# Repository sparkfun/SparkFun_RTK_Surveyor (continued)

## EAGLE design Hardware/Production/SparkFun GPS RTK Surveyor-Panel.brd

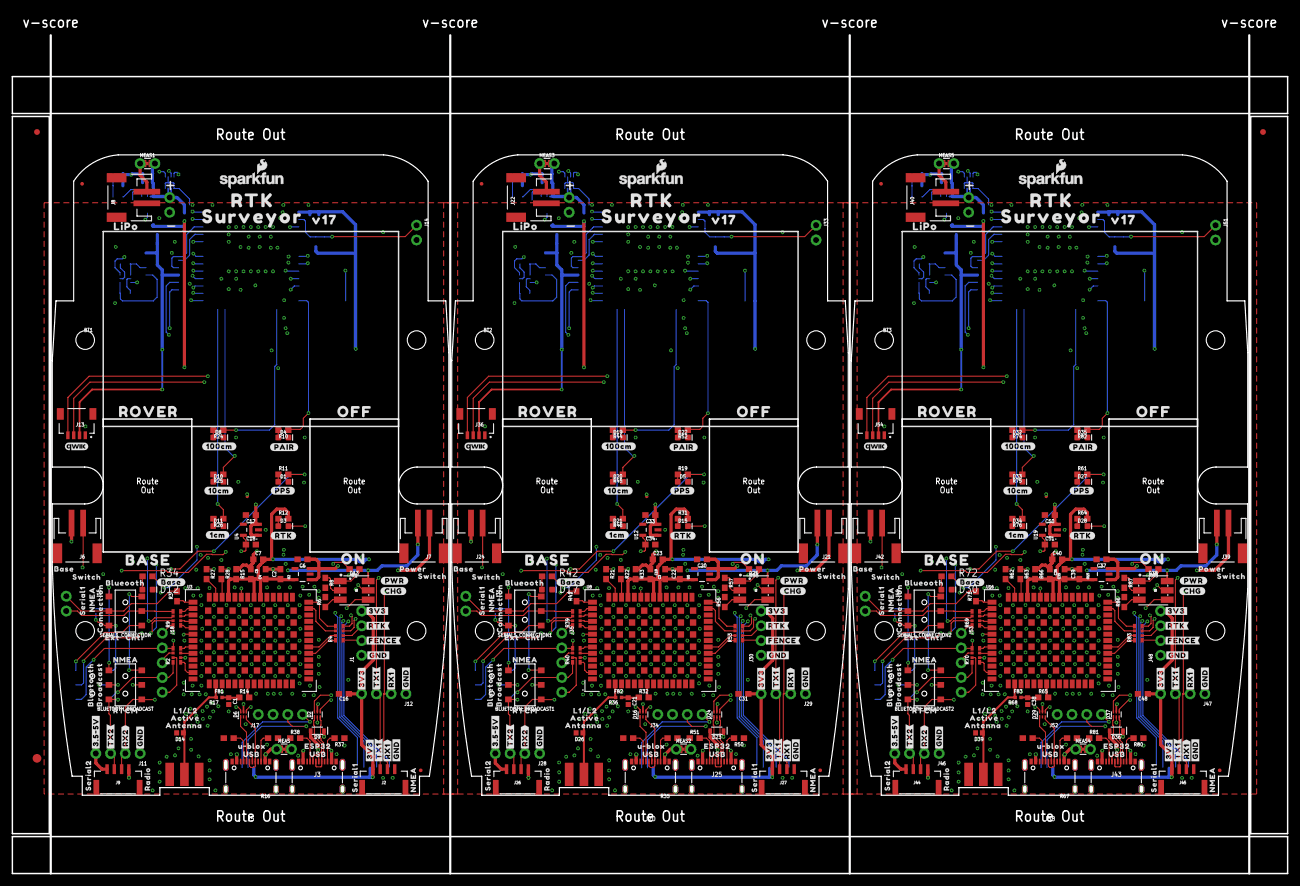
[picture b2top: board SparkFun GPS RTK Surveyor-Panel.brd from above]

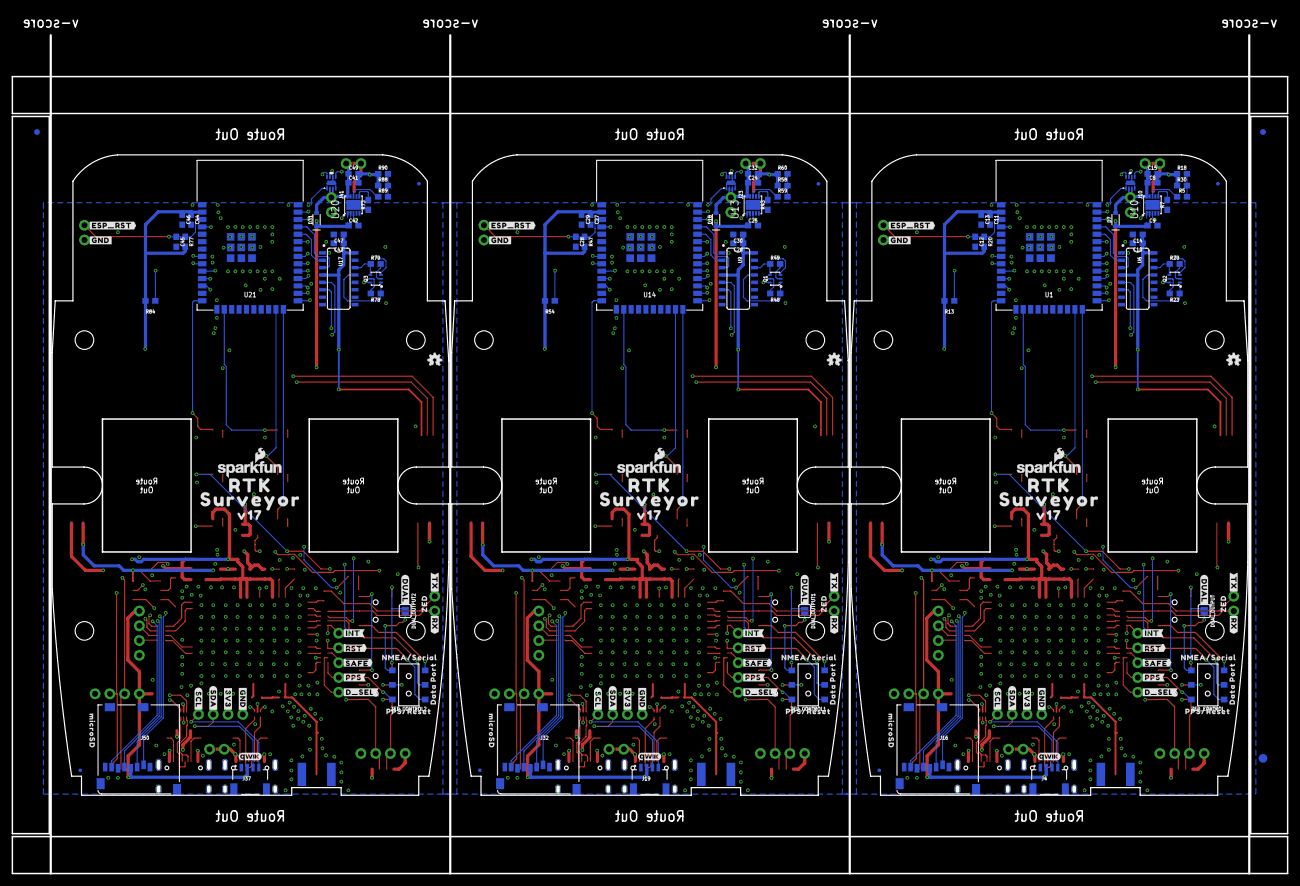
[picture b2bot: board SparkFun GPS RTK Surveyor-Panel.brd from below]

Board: 4 copper layers, 219.3 x 144.2 mm, 594 parts (168 on the bottom side), 285 nets.

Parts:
BLUETOOTH_BROADCAST, BLUETOOTH_BROADCAST1, BLUETOOTH_BROADCAST2: SWITCH_DPDT_SMD_AYZ0202
BT1, BT2, BT3: LIPO-OUTLINE1000; LIPO-1000
C1, C21, C38: 47pF; 0402
C2, C3, C4, C6, C17, C18, C20, C22, C33, C34, C35, C37, C39, C50, C51: 1.0uF; 0603
C5, C7, C11, C12, C13, C15, C16, C19, C23, C27, C28, C29, C31, C32, C36, C40, C44, C45, C46, C48, C49: 0.1uF; 0603
C8, C9, C24, C25, C41, C42: 4.7uF; 0603
C10, C14, C26, C30, C43, C47: 10uF; 0603
D1, D5, D27: Yellow; LED-0603
D2, D6, D16, D24, D29, D37: PRTR5V0U2F; SOT886
D3, D15, D28: WHITE; LED-0603
D4, D22, D35: BLUE; LED-0603
D7, D9, D18, D23, D31, D36: 3A/10V/280mV; SOD-323
D8, D10, D11, D19, D20, D21, D32, D33, D34: GREEN; LED-0603
D12, D17, D30: RED; LED-0603
D13, D25, D38: LED-TRICOLOR-5050
D14, D26, D39: PESD0402; 0402
DUAL_OUTPUT, DUAL_OUTPUT1, DUAL_OUTPUT2: SMT-JUMPER_2_NO_SILK
E1, E2, E3: SMA; SMA-EDGE
E$1, E$2, E$3, E$4: FIDUCIAL-1X2
E$5, E$6: FIDUCIAL-1.5X3
FB1, FB2, FB3: 2.66Ω; 0402-TIGHT
J1, J11, J12, J28, J29, J30, J46, J47, J48: 1X04_NO_SILK
J2, J9, J26, J27, J44, J45: JST-4-SMD-1.25MM-LOCKING
J3, J5, J20, J25, J38, J43: USB Female Type C Connector; USB-C-16P_4LAYER-PADS
J4, J19, J37: External; JST04_1MM_RA
J6, J24, J42: Start Base; JST-2-SMD
J7, J21, J39: Power Switch; JST-2-SMD
J8, J22, J40: JST-2-SMD
J10, J14, J15, J23, J31, J33, J41, J49, J51: 1X02_NO_SILK
J13, J36, J54: Internal; JST04_1MM_RA
J16, J32, J50: microSD; MICRO-SD-SOCKET
J17, J34, J52: Qwiic Right Angle; 1X04_NO_SILK
J18, J35, J53: 1X05_NO_SILK
JP1, JP2, JP3, JP4, JP5, JP6, JP7, JP8, JP21, JP61, JP71, JP81: FIDUCIALUFIDUCIAL; FIDUCIAL-MICRO
LOGO1, LOGO4, LOGO7: OSHW-LOGOMINI; OSHW-LOGO-MINI
LOGO2, LOGO3, LOGO5, LOGO6, LOGO8, LOGO9: SFE_LOGO_NAME_FLAME.1_INCH; SFE_LOGO_NAME_FLAME_.1
MEAS, MEAS1, MEAS2, MEAS3, MEAS4, MEAS5: COMBO-JUMPER_2_NC_TRACE
Q1, Q2, Q3: MBT3904DW1T1; SC70-6
R1, R55, R85: 4.7k; 0603
R2, R4, R9, R39, R40, R53, R69, R70, R83: 33; 1206_RA
R3, R41, R71: 33; 0603
R5, R59, R89: 0; 0603
R6, R7, R8, R43, R56, R57, R73, R86, R87: 1k; 0603
R10, R12, R31, R34, R42, R52, R64, R72, R82: 330; 0603
R11, R19, R24, R25, R26, R44, R45, R46, R61, R74, R75, R76: 20; 0603
R13, R15, R33, R54, R66, R84: 100k; 0603
R14, R32, R65: 10; 0603
R16, R17, R35, R36, R37, R38, R50, R51, R67, R68, R80, R81: 5.1k; 0603
R18, R20, R23, R29, R47, R48, R49, R60, R77, R78, R79, R90: 10k; 0603
R21, R22, R27, R28, R62, R63: 27; 0603
R30, R58, R88: 150k; 0603
SERIAL1_CONNECTION, SERIAL1_CONNECTION1, SERIAL1_CONNECTION2: SWITCH_DPDT_SMD_AYZ0202
U1, U14, U21: ESP-WROOM-3232D-NARROW; ESP-WROOM-32D-NARROW
U2, U4, U5, U12, U15, U19: 3.3V; SOT23-5
U3, U8, U16: U-BLOX_ZED-F9P; ZED-F9P
U6, U9, U17: CH340C; SO016
U7, U11, U18: MAX17048; DFN-8
U10, U13, U20: MCP73833; DFN-10
U$1, U$38, U$48, U$82, U$100, U$128, U$129, U$171, U$194, U$222, U$223, U$265: #GND#0
U$2, U$30, U$93, U$186, U$189, U$280: QWIIC_4MM
U$3, U$34, U$114, U$116, U$208, U$210: ROCKER_SWITCH
U$4, U$115, U$209: #BASE#0
U$5, U$37, U$47, U$99, U$127, U$168, U$193, U$221, U$262: #3V3#0
U$6, U$101, U$195: ANTENNA0
U$7, U$74, U$175, U$176, U$269, U$270: RTK0
U$8, U$108, U$202: #CHG#0
U$9, U$71, U$102, U$153, U$196, U$247: _SURVEYOR3
U$10, U$103, U$197: #RTK#1
U$11, U$152, U$246: #PPS#0
U$12, U$96, U$190: #RTK#0
U$13, U$15, U$21, U$69, U$75, U$76, U$77, U$78, U$117, U$118, U$151, U$158, U$159, U$160, U$161, U$162, U$211, U$212, U$245, U$252, U$253, U$254, U$255, U$256: LIGHT_PIPE_3MM
U$14, U$154, U$248: #RX#2
U$16, U$155, U$249: ZED0
U$17, U$133, U$227: ##SAFE##5
U$18, U$104, U$198: ACTIVE0
U$19, U$105, U$199: L1#L21
U$20, U$106, U$200: #PAIR#0
U$22, U$119, U$213: BASE2
U$23, U$140, U$234: #3#5#5V#0
U$24, U$97, U$191: #PPS#1
U$25, U$98, U$192: #PWR#2
U$26, U$107, U$201: 1553DBK-ENCLOSURE
U$27, U$109, U$203: LIPO0
U$28, U$132, U$226: ##RST##4
U$29, U$63, U$113, U$149, U$207, U$243: SERIAL10
U$31, U$120, U$214: OFF1
U$32, U$134, U$228: #FENCE#3
U$33, U$135, U$229: #INT#0
U$35, U$110, U$204: U#BLOX0
U$36, U$66, U$111, U$166, U$205, U$260: USB1
U$39, U$123, U$217: #RX2#2
U$40, U$124, U$218: #TX2#1
U$41, U$141, U$235: BLUETOOTH2
U$42, U$121, U$215: ON0
U$43, U$112, U$206: SERIAL20
U$44, U$122, U$216: ROVER3
U$45, U$68, U$125, U$170, U$219, U$264: #RX1#2
U$46, U$65, U$126, U$169, U$220, U$263: #TX1#1
U$49, U$52, U$130, U$143, U$224, U$237: NMEA1
U$50, U$131, U$225: RADIO0
U$51, U$142, U$236: BROADCAST3
U$53, U$144, U$238: RTCM0
U$54, U$136, U$230: BASE0
U$55, U$57, U$137, U$139, U$231, U$233: SWITCH1
U$56, U$138, U$232: POWER0
U$58, U$145, U$239: BLUEOOTH3
U$59, U$146, U$240: CNTR1
U$60, U$174, U$268: #ESP_RST#0
U$61, U$147, U$241: EXT0
U$62, U$148, U$242: NMEA2
U$64, U$150, U$244: CONNECTION1
U$67, U$167, U$261: ESP320
U$70, U$177, U$271: #GND#2
U$72, U$156, U$250: #TX#1
U$73, U$157, U$251: #DUAL#0
U$79, U$163, U$257: #1CM#0
U$80, U$164, U$258: #10CM#1
U$81, U$165, U$259: #100CM#2
U$83, U$172, U$266: MICROSD0
U$84, U$173, U$267: #GND#1
U$85, U$178, U$272: #3V3#2
U$86, U$179, U$273: #SCL#1
U$87, U$180, U$274: #SDA#0
U$88, U$181, U$275: #D_SEL#0
U$89, U$182, U$276: DATA2
U$90, U$183, U$277: PORT3
U$91, U$184, U$278: PPS#RESET0
U$92, U$185, U$279: NMEA#SERIAL1
U$94, U$95, U$187, U$188, U$281, U$282: V170
ZED_CONTROL, ZED_CONTROL1, ZED_CONTROL2: SWITCH_DPDT_SMD_AYZ0202

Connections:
3.3V: C2.1, C4.1, C5.2, C7.2, C10.1, C11.1, C13.1, C14.1, C16.1, J1.4, J2.1, J4.2, J12.4, J13.2, J16.VCC, J17.2, R12.2, R13.2, R15.2, R20.2, U1.2, U2.5, U3.33, U3.34, U3.38, U6.4, U6.16
3.3V1: C3.1, C19.2, C22.1, C23.2, C26.1, C27.1, C29.1, C30.1, C31.1, J19.2, J27.1, J29.4, J30.4, J32.VCC, J34.2, J36.2, R31.2, R33.2, R47.2, R54.2, U5.5, U8.33, U8.34, U8.38, U9.4, U9.16, U14.2
3.3V2: C35.1, C36.2, C39.1, C40.2, C43.1, C44.1, C46.1, C47.1, C48.1, J37.2, J45.1, J47.4, J48.4, J50.VCC, J52.2, J54.2, R64.2, R66.2, R77.2, R84.2, U15.5, U16.33, U16.34, U16.38, U17.4, U17.16, U21.2
5V: C6.1, J7.1, J9.1, J11.4, U2.1, U2.3
5V1: C20.1, J21.1, J26.1, J28.4, U5.1, U5.3
5V2: C37.1, J39.1, J44.1, J46.4, U15.1, U15.3
ANT_VCC: C1.1, FB1.2, R14.1
ANT_VCC1: C21.1, FB2.2, R32.1
ANT_VCC2: C38.1, FB3.2, R65.1
BACKUP: C18.1, U3.36, U4.5
BACKUP1: C34.1, U8.36, U12.5
BACKUP2: C51.1, U16.36, U19.5
CC1: J5.A5, R17.2
CC2: J5.B5, R16.2
CC3: J3.B5, R37.2
CC4: J3.A5, R38.2
CC5: J20.A5, R36.2
CC6: J20.B5, R35.2
CC7: J25.B5, R50.2
CC8: J25.A5, R51.2
CC9: J38.A5, R68.2
CC10: J38.B5, R67.2
CC11: J43.B5, R80.2
CC12: J43.A5, R81.2
CHG_LED: R1.2, U10.3
CHG_LED1: R55.2, U13.3
CHG_LED2: R85.2, U20.3
CHG_THERM1: R5.2, R18.2, R30.2
CHG_THERM2: R58.2, R59.2, R60.2
CHG_THERM3: R88.2, R89.2, R90.2
D+: D6.4, R27.1
D+1: D2.4, U6.5
D+2: D16.4, R21.1
D+3: D24.4, U9.5
D+4: D29.4, R62.1
D+5: D37.4, U17.5
D-: D6.6, R28.1
D-1: D2.6, U6.6
D-2: D16.6, R22.1
D-3: D24.6, U9.6
D-4: D29.6, R63.1
D-5: D37.6, U17.6
ESP32_!DTR: Q2.1, R23.1, U6.13
ESP32_!DTR1: Q1.1, R48.1, U9.13
ESP32_!DTR2: Q3.1, R78.1, U17.13
ESP32_!RTS: Q2.4, R29.1, U6.14
ESP32_!RTS1: Q1.4, R49.1, U9.14
ESP32_!RTS2: Q3.4, R79.1, U17.14
ESP32_EN: C12.1, J14.1, Q2.3, R20.1, U1.3
ESP32_EN1: C28.1, J33.1, Q1.3, R47.1, U14.3
ESP32_EN2: C45.1, J51.1, Q3.3, R77.1, U21.3
ESP32_RXI: U1.34, U6.2
ESP32_RXI1: U9.2, U14.34
ESP32_RXI2: U17.2, U21.34
ESP32_TXO: U1.35, U6.3
ESP32_TXO1: U9.3, U14.35
ESP32_TXO2: U17.3, U21.35
ESP_0/BOOT: Q2.6, U1.25
ESP_0/BOOT1: Q1.6, U14.25
ESP_0/BOOT2: Q3.6, U21.25
ESP_2/LED_1CM: R26.1, U1.24
ESP_2/LED_1CM1: R46.1, U14.24
ESP_2/LED_1CM2: R76.1, U21.24
ESP_4/LED_BASE_STAT: R34.1, U1.26
ESP_4/LED_BASE_STAT1: R42.1, U14.26
ESP_4/LED_BASE_STAT2: R72.1, U21.26
ESP_5/SWITCH_BASE_SELECT: J6.1, U1.29
ESP_5/SWITCH_BASE_SELECT1: J24.1, U14.29
ESP_5/SWITCH_BASE_SELECT2: J42.1, U21.29
ESP_12/LED_BLUETOOTH: R10.1, U1.14
ESP_12/LED_BLUETOOTH1: R52.1, U14.14
ESP_12/LED_BLUETOOTH2: R82.1, U21.14
ESP_13/LED_100CM: R24.1, U1.16
ESP_13/LED_100CM1: R44.1, U14.16
ESP_13/LED_100CM2: R74.1, U21.16
ESP_15/LED_10CM: R25.1, U1.23
ESP_15/LED_10CM1: R45.1, U14.23
ESP_15/LED_10CM2: R75.1, U21.23
ESP_16/BT_RXI: BLUETOOTH_BROADCAST.2, U1.27
ESP_16/BT_RXI1: BLUETOOTH_BROADCAST1.2, U14.27
ESP_16/BT_RXI2: BLUETOOTH_BROADCAST2.2, U21.27
ESP_17/BT_TXO: BLUETOOTH_BROADCAST.5, U1.28
ESP_17/BT_TXO1: BLUETOOTH_BROADCAST1.5, U14.28
ESP_17/BT_TXO2: BLUETOOTH_BROADCAST2.5, U21.28
ESP_18/SD_SCK: J16.SCLK, U1.30
ESP_18/SD_SCK1: J32.SCLK, U14.30
ESP_18/SD_SCK2: J50.SCLK, U21.30
ESP_19/SD_CIPO: J16.DO/DAT0, U1.31
ESP_19/SD_CIPO1: J32.DO/DAT0, U14.31
ESP_19/SD_CIPO2: J50.DO/DAT0, U21.31
ESP_21/SDA: J4.3, J13.3, J17.3, R9.P6, U1.33, U7.8
ESP_21/SDA1: J19.3, J34.3, J36.3, R39.P6, U11.8, U14.33
ESP_21/SDA2: J37.3, J52.3, J54.3, R69.P6, U18.8, U21.33
ESP_22/SCL: J4.4, J13.4, J17.4, R9.P7, U1.36, U7.7
ESP_22/SCL1: J19.4, J34.4, J36.4, R39.P7, U11.7, U14.36
ESP_22/SCL2: J37.4, J52.4, J54.4, R69.P7, U18.7, U21.36
ESP_23/SD_COPI: J16.DI/CMD, U1.37
ESP_23/SD_COPI1: J32.DI/CMD, U14.37
ESP_23/SD_COPI2: J50.DI/CMD, U21.37
ESP_25/SD_!CS!: J16.CS/DAT3, R13.1, U1.10
ESP_25/SD_!CS!1: J32.CS/DAT3, R54.1, U14.10
ESP_25/SD_!CS!2: J50.CS/DAT3, R84.1, U21.10
ESP_26/ZED_TX_READY: J18.1, R9.P8, U1.11
ESP_26/ZED_TX_READY1: J35.1, R39.P8, U14.11
ESP_26/ZED_TX_READY2: J53.1, R69.P8, U21.11
ESP_26/ZED_TX_READY_LV: R9.P1, U3.46
ESP_26/ZED_TX_READY_LV1: R39.P1, U8.46
ESP_26/ZED_TX_READY_LV2: R69.P1, U16.46
ESP_27/ZED_!RESET!: J18.2, R2.P5, U1.12, ZED_CONTROL.4
ESP_27/ZED_!RESET!1: J35.2, R40.P5, U14.12, ZED_CONTROL1.4
ESP_27/ZED_!RESET!2: J53.2, R70.P5, U21.12, ZED_CONTROL2.4
ESP_27/ZED_!RESET!_LV: R2.P4, U3.49
ESP_27/ZED_!RESET!_LV1: R40.P4, U8.49
ESP_27/ZED_!RESET!_LV2: R70.P4, U16.49
ESP_32/PWR_LVL_RED: D13.5, U1.8
ESP_32/PWR_LVL_RED1: D25.5, U14.8
ESP_32/PWR_LVL_RED2: D38.5, U21.8
ESP_33/PWR_LVL_GRN: D13.4, U1.9
ESP_33/PWR_LVL_GRN1: D25.4, U14.9
ESP_33/PWR_LVL_GRN2: D38.4, U21.9
ESP_36/BATT_ALRT: U1.4, U7.5
ESP_36/BATT_ALRT1: U11.5, U14.4
ESP_36/BATT_ALRT2: U18.5, U21.4
ESP_D1+: D2.3, J3.A6, J3.B6
ESP_D1+1: D24.3, J25.A6, J25.B6
ESP_D1+2: D37.3, J43.A6, J43.B6
ESP_D1-: D2.1, J3.A7, J3.B7
ESP_D1-1: D24.1, J25.A7, J25.B7
ESP_D1-2: D37.1, J43.A7, J43.B7
EXTERNAL_SERIAL1_RXI: SERIAL1_CONNECTION.4, ZED_CONTROL.6
EXTERNAL_SERIAL1_RXI1: SERIAL1_CONNECTION1.4, ZED_CONTROL1.6
EXTERNAL_SERIAL1_RXI2: SERIAL1_CONNECTION2.4, ZED_CONTROL2.6
EXTERNAL_SERIAL1_RXI/ZED_!RESET!: J2.3, J12.2, ZED_CONTROL.5
EXTERNAL_SERIAL1_RXI/ZED_!RESET!1: J27.3, J29.2, ZED_CONTROL1.5
EXTERNAL_SERIAL1_RXI/ZED_!RESET!2: J45.3, J47.2, ZED_CONTROL2.5
EXTERNAL_SERIAL1_TXO: DUAL_OUTPUT.2, SERIAL1_CONNECTION.1, ZED_CONTROL.3
EXTERNAL_SERIAL1_TXO1: DUAL_OUTPUT1.2, SERIAL1_CONNECTION1.1, ZED_CONTROL1.3
EXTERNAL_SERIAL1_TXO2: DUAL_OUTPUT2.2, SERIAL1_CONNECTION2.1, ZED_CONTROL2.3
EXTERNAL_SERIAL1_TXO/PPS: J2.2, J12.3, ZED_CONTROL.2
EXTERNAL_SERIAL1_TXO/PPS1: J27.2, J29.3, ZED_CONTROL1.2
EXTERNAL_SERIAL1_TXO/PPS2: J45.2, J47.3, ZED_CONTROL2.2
FENCE_LV: R4.P8, U3.19
FENCE_LV1: R53.P8, U8.19
FENCE_LV2: R83.P8, U16.19
GND: C1.2, C2.2, C4.2, C5.1, C6.2, C7.1, C8.2, C9.2, C10.2, C11.2, C12.2, C13.2, C14.2, C15.2, C16.2, C17.2, C18.2, D1.C, D2.2, D4.C, D6.2, D8.C, D10.C, D11.C, D12.C, D14.2, E1.GND@0, E1.GND@1, E1.GND@2, E1.GND@3, J1.1, J2.4, J3.GND, J3.GND2, J3.SHLD1, J3.SHLD2, J3.SHLD3, J3.SHLD4, J4.1, J5.GND, J5.GND2, J5.SHLD1, J5.SHLD2, J5.SHLD3, J5.SHLD4, J6.2, J8.1, J9.4, J10.2, J11.1, J12.1, J13.1, J14.2, J16.CD1, J16.GND, J16.GND1, J16.GND3, J17.1, R6.2, R7.1, R8.2, R15.1, R16.1, R17.1, R18.1, R30.1, R37.1, R38.1, U1.1, U1.15, U1.38, U1.GND1, U1.GNDT1, U1.GNDT2, U1.GNDT3, U1.GNDT4, U1.GNDT5, U1.GNDT6, U1.GNDT7, U1.GNDT8, U2.2, U3.1, U3.3, U3.12, U3.14, U3.32, U3.37, U3.41, U3.48, U3.55, U3.56, U3.57, U3.58, U3.59, U3.60, U3.61, U3.62, U3.63, U3.64, U3.65, U3.66, U3.67, U3.68, U3.69, U3.70, U3.71, U3.72, U3.73, U3.74, U3.75, U3.76, U3.77, U3.78, U3.79, U3.80, U3.81, U3.82, U3.83, U3.84, U3.85, U3.86, U3.87, U3.88, U3.89, U3.90, U3.91, U3.92, U3.93, U3.94, U3.95, U3.96, U3.97, U3.98, U3.99, U3.100, U3.101, U3.102, U4.2, U6.1, U7.1, U7.4, U7.6, U7.9, U10.5, U10.11
GND1: C3.2, C19.1, C20.2, C21.2, C22.2, C23.1, C24.2, C25.2, C26.2, C27.2, C28.2, C29.2, C30.2, C31.2, C32.2, C33.2, C34.2, D5.C, D16.2, D17.C, D19.C, D20.C, D21.C, D22.C, D24.2, D26.2, E2.GND@0, E2.GND@1, E2.GND@2, E2.GND@3, J19.1, J20.GND, J20.GND2, J20.SHLD1, J20.SHLD2, J20.SHLD3, J20.SHLD4, J22.1, J23.2, J24.2, J25.GND, J25.GND2, J25.SHLD1, J25.SHLD2, J25.SHLD3, J25.SHLD4, J26.4, J27.4, J28.1, J29.1, J30.1, J32.CD1, J32.GND, J32.GND1, J32.GND3, J33.2, J34.1, J36.1, R33.1, R35.1, R36.1, R43.1, R50.1, R51.1, R56.2, R57.2, R58.1, R60.1, U5.2, U8.1, U8.3, U8.12, U8.14, U8.32, U8.37, U8.41, U8.48, U8.55, U8.56, U8.57, U8.58, U8.59, U8.60, U8.61, U8.62, U8.63, U8.64, U8.65, U8.66, U8.67, U8.68, U8.69, U8.70, U8.71, U8.72, U8.73, U8.74, U8.75, U8.76, U8.77, U8.78, U8.79, U8.80, U8.81, U8.82, U8.83, U8.84, U8.85, U8.86, U8.87, U8.88, U8.89, U8.90, U8.91, U8.92, U8.93, U8.94, U8.95, U8.96, U8.97, U8.98, U8.99, U8.100, U8.101, U8.102, U9.1, U11.1, U11.4, U11.6, U11.9, U12.2, U13.5, U13.11, U14.1, U14.15, U14.38, U14.GND1, U14.GNDT1, U14.GNDT2, U14.GNDT3, U14.GNDT4, U14.GNDT5, U14.GNDT6, U14.GNDT7, U14.GNDT8
GND2: C35.2, C36.1, C37.2, C38.2, C39.2, C40.1, C41.2, C42.2, C43.2, C44.2, C45.2, C46.2, C47.2, C48.2, C49.2, C50.2, C51.2, D27.C, D29.2, D30.C, D32.C, D33.C, D34.C, D35.C, D37.2, D39.2, E3.GND@0, E3.GND@1, E3.GND@2, E3.GND@3, J37.1, J38.GND, J38.GND2, J38.SHLD1, J38.SHLD2, J38.SHLD3, J38.SHLD4, J40.1, J41.2, J42.2, J43.GND, J43.GND2, J43.SHLD1, J43.SHLD2, J43.SHLD3, J43.SHLD4, J44.4, J45.4, J46.1, J47.1, J48.1, J50.CD1, J50.GND, J50.GND1, J50.GND3, J51.2, J52.1, J54.1, R66.1, R67.1, R68.1, R73.1, R80.1, R81.1, R86.2, R87.2, R88.1, R90.1, U15.2, U16.1, U16.3, U16.12, U16.14, U16.32, U16.37, U16.41, U16.48, U16.55, U16.56, U16.57, U16.58, U16.59, U16.60, U16.61, U16.62, U16.63, U16.64, U16.65, U16.66, U16.67, U16.68, U16.69, U16.70, U16.71, U16.72, U16.73, U16.74, U16.75, U16.76, U16.77, U16.78, U16.79, U16.80, U16.81, U16.82, U16.83, U16.84, U16.85, U16.86, U16.87, U16.88, U16.89, U16.90, U16.91, U16.92, U16.93, U16.94, U16.95, U16.96, U16.97, U16.98, U16.99, U16.100, U16.101, U16.102, U17.1, U18.1, U18.4, U18.6, U18.9, U19.2, U20.5, U20.11, U21.1, U21.15, U21.38, U21.GND1, U21.GNDT1, U21.GNDT2, U21.GNDT3, U21.GNDT4, U21.GNDT5, U21.GNDT6, U21.GNDT7, U21.GNDT8
GPS_ANT1: D14.1, E1.SIG, FB1.1, U3.2
GPS_ANT2: D26.1, E2.SIG, FB2.1, U8.2
GPS_ANT3: D39.1, E3.SIG, FB3.1, U16.2
LIPO_RAW: J8.2, MEAS1.1, MEAS1.3
LIPO_RAW1: J22.2, MEAS3.1, MEAS3.3
LIPO_RAW2: J40.2, MEAS5.1, MEAS5.3
unnamed: D3.A, R12.1
unnamed: D1.A, R11.1
unnamed: D4.A, R10.2
unnamed: J5.VBUS1, J5.VBUS2, MEAS.1, MEAS.3
unnamed: R5.1, U10.8
unnamed: D13.1, R1.1
unnamed: D13.3, R6.1
unnamed: D13.2, R8.1
unnamed: D5.A, R19.1
unnamed: R21.2, U8.40
unnamed: R27.2, U3.40
unnamed: R28.2, U3.39
unnamed: R14.2, U3.7
unnamed: R22.2, U8.39
unnamed: D15.A, R31.1
unnamed: R32.2, U8.7
unnamed: D17.A, R42.2
unnamed: D19.A, R44.2
unnamed: D20.A, R45.2
unnamed: D21.A, R46.2
unnamed: Q1.5, R48.2
unnamed: Q1.2, R49.2
unnamed: D23.A, J25.VBUS1, J25.VBUS2
unnamed: Q2.5, R23.2
unnamed: Q2.2, R29.2
unnamed: D8.A, R24.2
unnamed: D10.A, R25.2
unnamed: D22.A, R52.2
unnamed: D11.A, R26.2
unnamed: D12.A, R34.2
unnamed: J20.VBUS1, J20.VBUS2, MEAS2.1, MEAS2.3
unnamed: D9.A, J3.VBUS1, J3.VBUS2
unnamed: R59.1, U13.8
unnamed: D25.1, R55.1
unnamed: D25.3, R56.1
unnamed: D25.2, R57.1
unnamed: D27.A, R61.1
unnamed: R62.2, U16.40
unnamed: R63.2, U16.39
unnamed: D28.A, R64.1
unnamed: R65.2, U16.7
unnamed: D30.A, R72.2
unnamed: D32.A, R74.2
unnamed: D33.A, R75.2
unnamed: D34.A, R76.2
unnamed: Q3.5, R78.2
unnamed: Q3.2, R79.2
unnamed: D36.A, J43.VBUS1, J43.VBUS2
unnamed: D35.A, R82.2
unnamed: J38.VBUS1, J38.VBUS2, MEAS4.1, MEAS4.3
unnamed: R89.1, U20.8
unnamed: D38.1, R85.1
unnamed: D38.3, R86.1
unnamed: D38.2, R87.1
NMEA-RX: BLUETOOTH_BROADCAST.6, SERIAL1_CONNECTION.6
NMEA-RX1: BLUETOOTH_BROADCAST1.6, SERIAL1_CONNECTION1.6
NMEA-RX2: BLUETOOTH_BROADCAST2.6, SERIAL1_CONNECTION2.6
NMEA-TX: BLUETOOTH_BROADCAST.3, DUAL_OUTPUT.1, SERIAL1_CONNECTION.3
NMEA-TX1: BLUETOOTH_BROADCAST1.3, DUAL_OUTPUT1.1, SERIAL1_CONNECTION1.3
NMEA-TX2: BLUETOOTH_BROADCAST2.3, DUAL_OUTPUT2.1, SERIAL1_CONNECTION2.3
PPS: R2.P1, U3.53
PPS1: R40.P1, U8.53
PPS2: R70.P1, U16.53
PROG1: R7.2, U10.6
PROG2: R43.2, U13.6
PROG3: R73.2, U20.6
RTK_LV: R4.P7, U3.20
RTK_LV1: R53.P7, U8.20
RTK_LV2: R83.P7, U16.20
RX2_LV: R4.P6, U3.26
RX2_LV1: R53.P6, U8.26
RX2_LV2: R83.P6, U16.26
RXLV: R9.P4, U3.43
RXLV1: R39.P4, U8.43
RXLV2: R69.P4, U16.43
SCL_LV: R9.P2, U3.45
SCL_LV1: R39.P2, U8.45
SCL_LV2: R69.P2, U16.45
SDA_LV: R9.P3, U3.44
SDA_LV1: R39.P3, U8.44
SDA_LV2: R69.P3, U16.44
TX2_LV: R4.P5, U3.27
TX2_LV1: R53.P5, U8.27
TX2_LV2: R83.P5, U16.27
TXLV: R3.1, U3.42
TXLV1: R41.1, U8.42
TXLV2: R71.1, U16.42
UNP_D+: D6.3, J5.A6, J5.B6
UNP_D+1: D16.3, J20.A6, J20.B6
UNP_D+2: D29.3, J38.A6, J38.B6
UNP_D-: D6.1, J5.A7, J5.B7
UNP_D-1: D16.1, J20.A7, J20.B7
UNP_D-2: D29.1, J38.A7, J38.B7
VIN: C9.1, D2.5, D6.5, D7.C, D9.C, D13.6, J7.2, MEAS.2, MEAS.4, U10.1, U10.2
VIN1: C25.1, D16.5, D18.C, D23.C, D24.5, D25.6, J21.2, MEAS2.2, MEAS2.4, U13.1, U13.2
VIN2: C42.1, D29.5, D31.C, D36.C, D37.5, D38.6, J39.2, MEAS4.2, MEAS4.4, U20.1, U20.2
V_BATT: C8.1, C15.1, C17.1, D7.A, J10.1, MEAS1.2, MEAS1.4, U4.1, U4.3, U7.2, U7.3, U10.9, U10.10
V_BATT1: C24.1, C32.1, C33.1, D18.A, J23.1, MEAS3.2, MEAS3.4, U11.2, U11.3, U12.1, U12.3, U13.9, U13.10
V_BATT2: C41.1, C49.1, C50.1, D31.A, J41.1, MEAS5.2, MEAS5.4, U18.2, U18.3, U19.1, U19.3, U20.9, U20.10
ZED-RXI1: J15.2, R9.P5, SERIAL1_CONNECTION.5
ZED-RXI2: BLUETOOTH_BROADCAST.4, J9.3, J11.2, R4.P3
ZED-RXI3: BLUETOOTH_BROADCAST1.4, J26.3, J28.2, R53.P3
ZED-RXI4: J31.2, R39.P5, SERIAL1_CONNECTION1.5
ZED-RXI5: BLUETOOTH_BROADCAST2.4, J44.3, J46.2, R83.P3
ZED-RXI6: J49.2, R69.P5, SERIAL1_CONNECTION2.5
ZED-TXO1: J15.1, R3.2, SERIAL1_CONNECTION.2
ZED-TXO2: BLUETOOTH_BROADCAST.1, J9.2, J11.3, R4.P4
ZED-TXO3: J31.1, R41.2, SERIAL1_CONNECTION1.2
ZED-TXO4: BLUETOOTH_BROADCAST1.1, J26.2, J28.3, R53.P4
ZED-TXO5: J49.1, R71.2, SERIAL1_CONNECTION2.2
ZED-TXO6: BLUETOOTH_BROADCAST2.1, J44.2, J46.3, R83.P4
ZED_!SAFE!: J18.3, R2.P6
ZED_!SAFE!1: J35.3, R40.P6
ZED_!SAFE!2: J53.3, R70.P6
ZED_!SAFE!_LV: R2.P3, U3.50
ZED_!SAFE!_LV1: R40.P3, U8.50
ZED_!SAFE!_LV2: R70.P3, U16.50
ZED_D_SEL: J18.5, R2.P7
ZED_D_SEL1: J35.5, R40.P7
ZED_D_SEL2: J53.5, R70.P7
ZED_D_SEL_LV: R2.P2, U3.47
ZED_D_SEL_LV1: R40.P2, U8.47
ZED_D_SEL_LV2: R70.P2, U16.47
ZED_FENCE_STAT: J1.2, R4.P1
ZED_FENCE_STAT1: J30.2, R53.P1
ZED_FENCE_STAT2: J48.2, R83.P1
ZED_PPS_STAT: J18.4, R2.P8, R11.2, ZED_CONTROL.1
ZED_PPS_STAT1: J35.4, R19.2, R40.P8, ZED_CONTROL1.1
ZED_PPS_STAT2: J53.4, R61.2, R70.P8, ZED_CONTROL2.1
ZED_RTK_STAT: D3.C, J1.3, R4.P2
ZED_RTK_STAT1: D15.C, J30.3, R53.P2
ZED_RTK_STAT2: D28.C, J48.3, R83.P2

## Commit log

2021-07-01 Replace SMA SMD with edge mount SMA. v17 PCB
2021-07-01 Update panel to v17
2022-02-03 Update issue templates
2022-03-30 Add route out note
2022-03-30 Remove graphics files
2024-12-20 Add 3D enclosure file
